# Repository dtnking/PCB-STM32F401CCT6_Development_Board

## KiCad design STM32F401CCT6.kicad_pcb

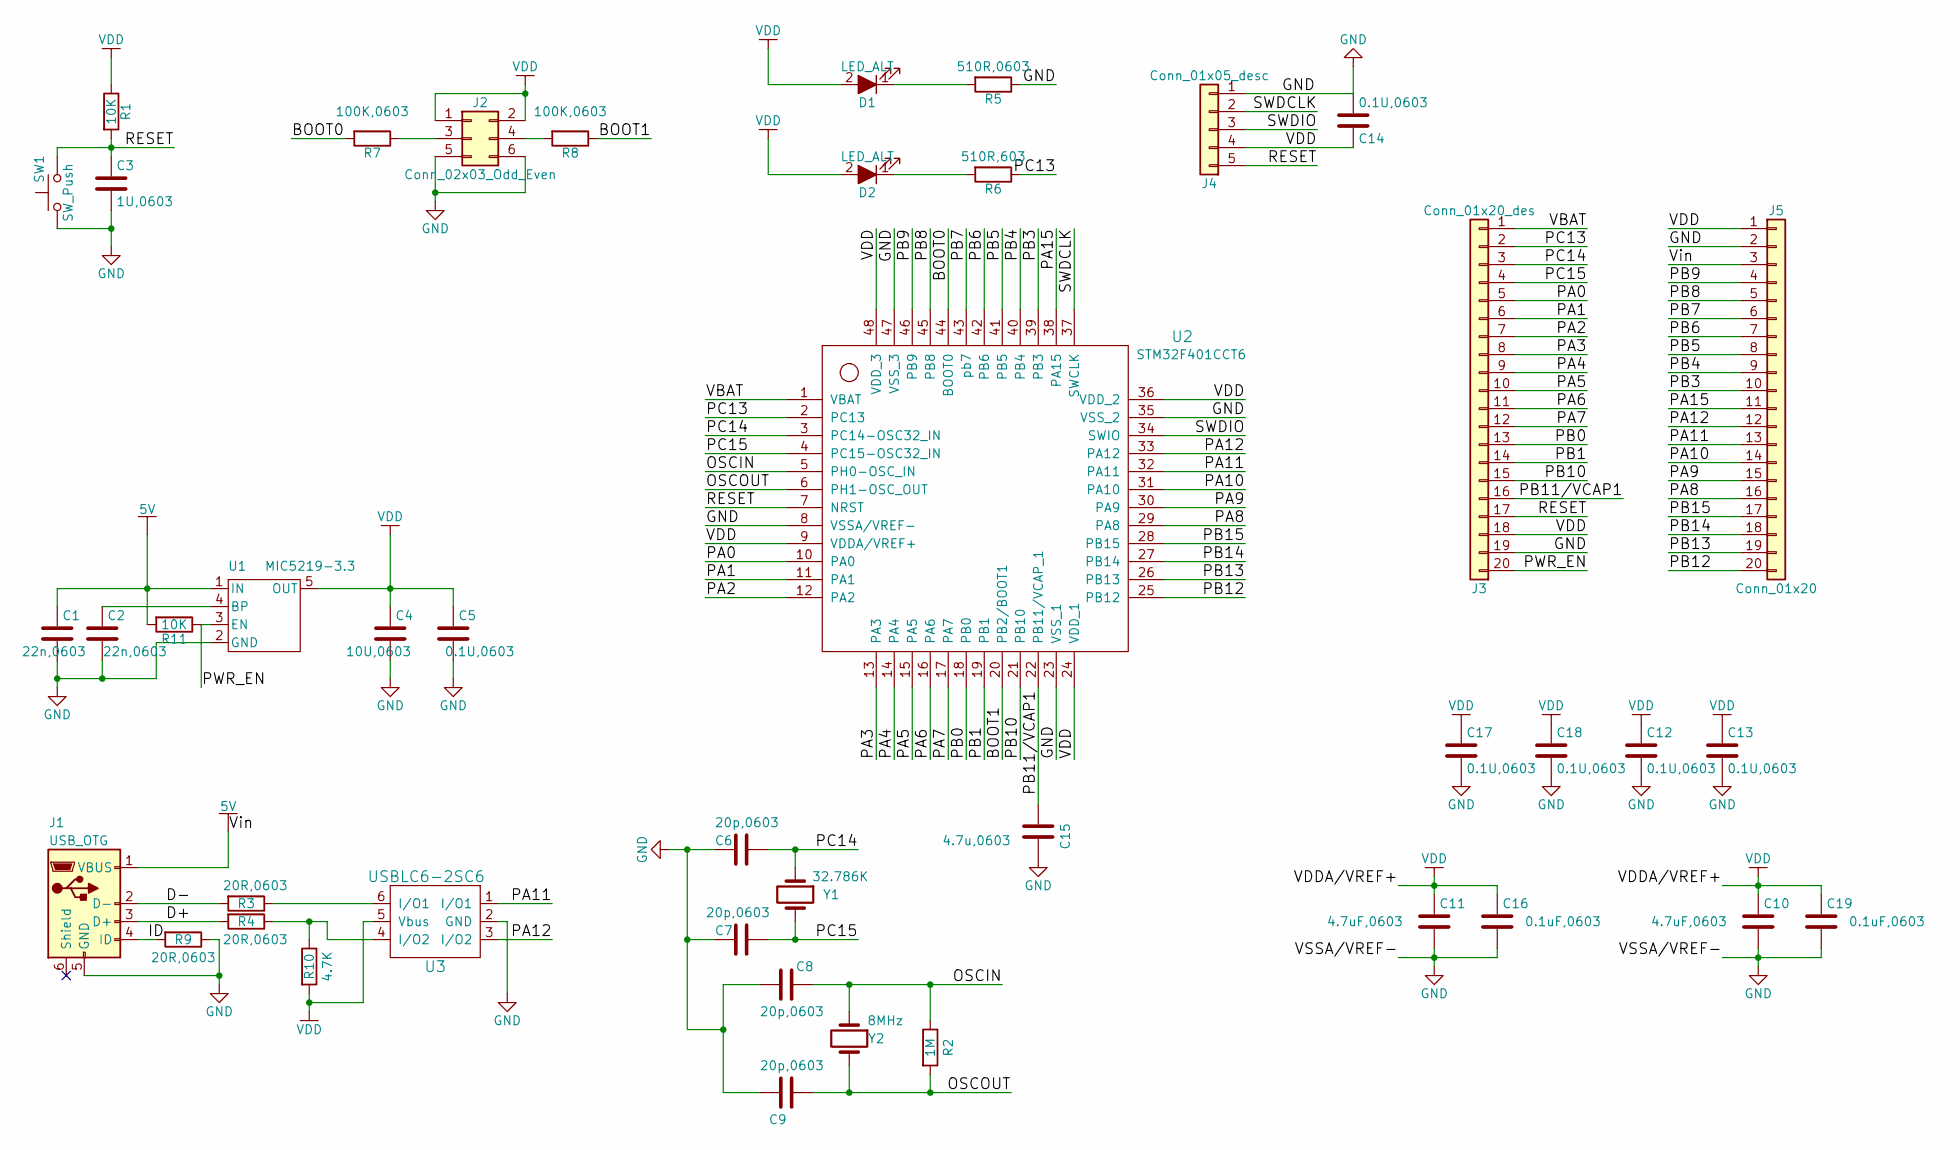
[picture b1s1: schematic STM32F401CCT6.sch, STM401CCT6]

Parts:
C1, C2: 22n,0603; C_0603
C3: 1U,0603; C_0603
C4: 10U,0603; C_0603
C5, C12, C13, C14, C17, C18: 0.1U,0603; C_0603
C6, C7, C8, C9: 20p,0603; C_0603
C10, C11: 4.7uF,0603; C_0603
C15: 4.7u,0603; C_0603
C16, C19: 0.1uF,0603; C_0603
D1, D2: LED_ALT; LED_0805
J1: USB_OTG; USB_Micro-B_Molex-105017-0001
J2: Conn_02x03_Odd_Even; Pin_Header_Straight_2x03_Pitch2.54mm
J3: Conn_01x20_des; Pin_Header_Straight_1x20_Pitch2.54mm
J4: Conn_01x05_desc; Pin_Header_Angled_1x05_Pitch2.54mm
J5: Conn_01x20; Pin_Header_Straight_1x20_Pitch2.54mm
R1, R11: 10K; R_0603
R2: 1M; R_0603
R3, R4, R9: 20R,0603; R_0603
R5: 510R,0603; R_0603
R6: 510R,603; R_0603
R7, R8: 100K,0603; R_0603
R10: 4.7K; R_0603
SW1: SW_Push; SW_SPST_TL3342
U1: MIC5219-3.3; SOT-23-5
U2: STM32F401CCT6; QFN_QFP48
U3: USBLC6-2SC6; SOT-23-6
Y1: 32.786K; Crystal_SMD_SeikoEpson_MC306-4pin_8.0x3.2mm
Y2: 8MHz; Crystal_HC49-4H_Vertical

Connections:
+5V: C1.1, J1.1 (VBUS), J5.3, R11.2, U1.1 (IN)
/BOOT0: R7.2, U2.44 (BOOT0)
/BOOT1: R8.1, U2.20 (PB2/BOOT1)
/D+: J1.3 (D+), R4.2
/D-: J1.2 (D-), R3.2
/ID: J1.4 (ID), R9.2
/OSCIN: C8.1, R2.1, U2.5 (PH0-OSC_IN), Y2.1
/OSCOUT: C9.1, R2.2, U2.6 (PH1-OSC_OUT), Y2.2
/PA0: J3.5, U2.10 (PA0)
/PA1: J3.6, U2.11 (PA1)
/PA2: J3.7, U2.12 (PA2)
/PA3: J3.8, U2.13 (PA3)
/PA4: J3.9, U2.14 (PA4)
/PA5: J3.10, U2.15 (PA5)
/PA6: J3.11, U2.16 (PA6)
/PA7: J3.12, U2.17 (PA7)
/PA8: J5.16, U2.29 (PA8)
/PA9: J5.15, U2.30 (PA9)
/PA10: J5.14, U2.31 (PA10)
/PA11: J5.13, U2.32 (PA11), U3.1 (I/O1)
/PA12: J5.12, U2.33 (PA12), U3.3 (I/O2)
/PA15: J5.11, U2.38 (PA15)
/PB0: J3.13, U2.18 (PB0)
/PB1: J3.14, U2.19 (PB1)
/PB3: J5.10, U2.39 (PB3)
/PB4: J5.9, U2.40 (PB4)
/PB5: J5.8, U2.41 (PB5)
/PB6: J5.7, U2.42 (PB6)
/PB7: J5.6, U2.43 (pb7)
/PB8: J5.5, U2.45 (PB8)
/PB9: J5.4, U2.46 (PB9)
/PB10: J3.15, U2.21 (PB10)
/PB11/VCAP1: C15.2, J3.16, U2.22 (PB11/VCAP_1)
/PB12: J5.20, U2.25 (PB12)
/PB13: J5.19, U2.26 (PB13)
/PB14: J5.18, U2.27 (PB14)
/PB15: J5.17, U2.28 (PB15)
/PC13: J3.2, R6.1, U2.2 (PC13)
/PC14: C6.1, J3.3, U2.3 (PC14-OSC32_IN), Y1.1
/PC15: C7.1, J3.4, U2.4 (PC15-OSC32_IN), Y1.2, Y1.4
/PWR_EN: J3.20, R11.1, U1.3 (EN)
/RESET: C3.1, J3.17, J4.5, R1.2, SW1.2, U2.7 (NRST)
/SWDCLK: J4.2, U2.37 (SWCLK)
/SWDIO: J4.3, U2.34 (SWIO)
/VBAT: J3.1, U2.1 (VBAT)
/VDD: C4.1, C5.1, C10.1, C11.1, C12.1, C13.1, C14.1, C16.1, C17.1, C18.1, C19.1, D1.2 (A), D2.2 (A), J2.1, J2.2, J3.18, J4.4, J5.1, R1.1, R10.2, U1.5 (OUT), U2.9 (VDDA/VREF+), U2.24 (VDD_1), U2.36 (VDD_2), U2.48 (VDD_3), U3.5 (Vbus)
GND: C1.2, C2.2, C3.2, C4.2, C5.2, C6.2, C7.2, C8.2, C9.2, C10.2, C11.2, C12.2, C13.2, C14.2, C15.1, C16.2, C17.2, C18.2, C19.2, J1.5 (GND), J1.6 (Shield), J2.5, J2.6, J3.19, J4.1, J5.2, R5.1, R9.1, SW1.1, U1.2 (GND), U2.0, U2.8 (VSSA/VREF-), U2.23 (VSS_1), U2.35 (VSS_2), U2.47 (VSS_3), U3.2 (GND)
unnamed: C2.1, U1.4 (BP)
unnamed: D1.1 (K), R5.2
unnamed: D2.1 (K), R6.2
unnamed: J2.3, R7.1
unnamed: J2.4, R8.2
unnamed: R3.1, U3.6 (I/O1)
unnamed: R4.1, R10.1, U3.4 (I/O2)

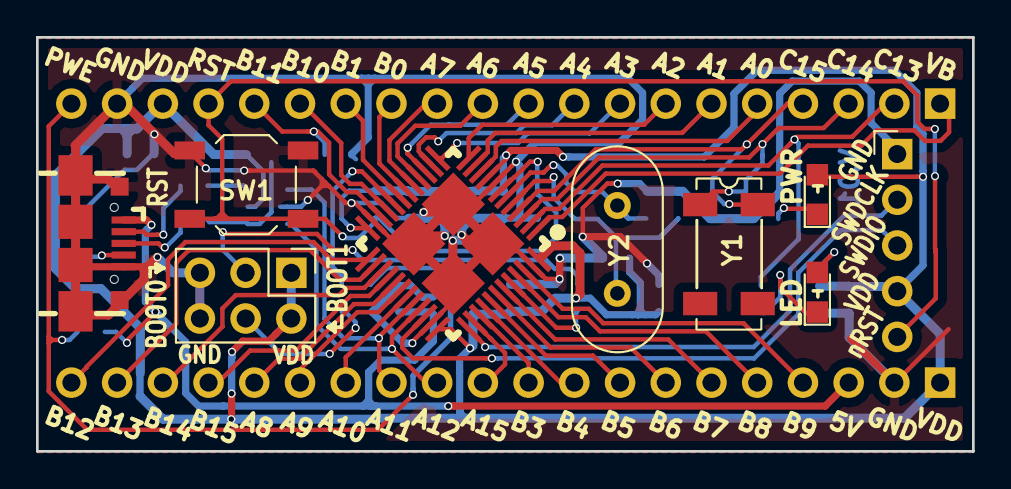
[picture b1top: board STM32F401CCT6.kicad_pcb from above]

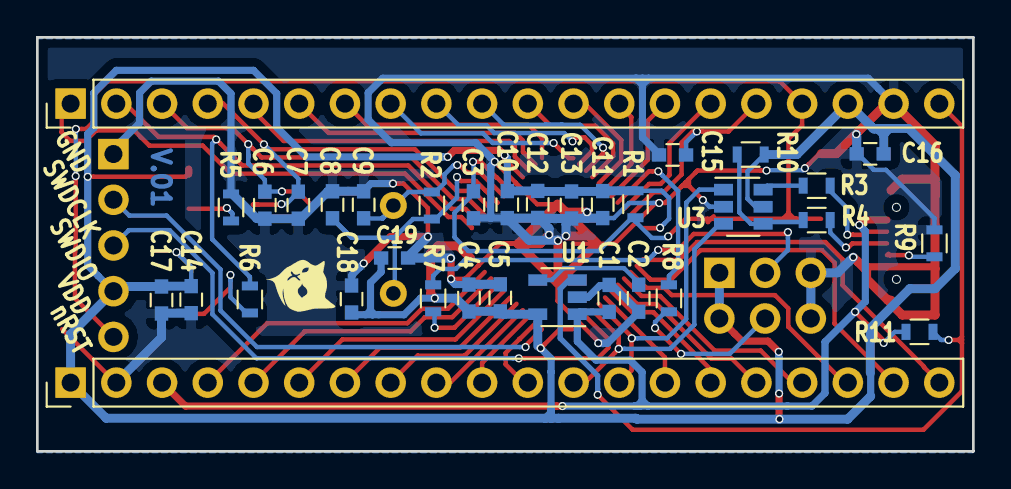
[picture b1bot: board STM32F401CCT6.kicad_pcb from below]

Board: 2 copper layers, 52.0 x 23.0 mm, 47 parts (35 on the bottom side), 54 nets.

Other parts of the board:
Dot: G***; Dot
HS_Crystal: G***; HS_Crystal
LS_Crystal: G***; LS_Crystal
Meow: G***; Meow

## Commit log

2017-10-03 Drawed the schematic of STM32F401CCT6-without TVS
2017-10-03 Added USBLC6 component lib
2017-10-05 Changed pin SWDIO and SWDCLK
2017-10-06 Assosciated schematic to footprint
2017-10-06 Changed LED(schematic)
2017-10-06 Added QFP-QFN48 footprint
2017-10-07 Fixed QFN-QPN mod
2017-10-07 Added a dot near pin1 as an indication
2017-10-09 routing
2017-10-10 Added copper pour
2017-10-10 Modified QFN-QFP48
2017-10-10 Rerouted
2017-10-11 rerouting (left reset)
2017-10-11 Fixed QFPN48 pin 47 and 48 distances to 0.2
2017-10-11 Finish routing
2017-10-12 Added pin name on silk layer
2017-10-12 Finish design the layout-Added Image on it
2017-10-13 Changed footprint from handsoldering to none
2017-10-13 Moved the pin connector to bottom layer
2017-10-13 Rotated the neko image
2017-10-17 Changed via size to 0.45/0.3mm and generated Gerber file
2017-10-20 Modified routing
2017-10-22 Moved the pin indicator(silk layer) further away from the edge cut
2017-10-23 Moved Micro_USB further out and reroute some tracks
2017-10-24 Moved the bottom edge cut further inwards
2017-10-30 Widen the track of power source
2017-10-30 Added corner outline as an indicator for the footprint QFP48
2017-10-31 Adjusted the size of the label indicator
2017-11-05 Updated the via diamter and drill size 0.435/0.3 mm
2017-11-06 Added extra capacitor between VDD and GND (VFFA-VSSA)
2017-11-06 Fixed the pad near tracks error (reallocated the QFN)
2017-11-07 Change pin20 to Pwr Enable and added a resistor on it
2017-11-07 Changed pin 20 to PWE schemaic
2017-11-09 Re-routed (prioritised D+ D- SWDIO SWCLK) by reducing the track length and via along the tracks.
2017-11-09 Changed the via size to 0.453/0.3 mm
2017-11-12 Renamed VCC to VDD
2017-11-13 Added indication for LED footprint and added dimension on Eco1.user layer
2017-11-14 Change the route nicely
2017-11-15 Panelized with other PCB
2017-11-16 Removed the silk layer of angled pin header and move the bottom pin label downward
2017-11-16 Produced merged gerber file of STM32 board together with RJ12 and ST-Link
2017-11-16 Changed the 4 corner labels indication for footprint of QFN-QFP
2017-11-17 Found missing bottom silk layer, placed it back
2017-11-17 Enlarged the QFN-QFP48 footprint pin 1 indication label and the dimension label from 0.3mm to 0.4mm
2017-11-17 Regenerated combined gerber file (with ST-Link and RJ12)
2017-11-17 Removed older PCB file
2017-11-17 Renamed the merge gerber folder
2017-11-17 Renamed the pin3 track label from ST-Link to Vin
2017-11-18 Moved silk layer away from via and swap the position of VDD with nRST pin of the SWDIO
2017-11-20 Added a new footprint for Micro USB (non-Complete)
2017-11-21 Extend the pads of the Micro-USB and draw the silk layer for indicatiom
2017-11-22 Replace the Micro-USB footprint with the one newly created, added a shield for MCU (grounded pin), moved some component inwards to prevent touching the pinheader plastic.
2017-11-22 Re-generated gerber files for panelizing
2017-11-27 Generated new gerber file
2017-11-29 Moved the indicator of LED slightly to the right
2017-12-01 Replaced the MCU footprint
2017-12-03 Changed the kitty silk layer
2017-12-05 changed the copper pour clearance
2017-12-10 Change back the Micro_usb footprint to THT footprint
2018-01-16 Generated gerber file with drill hole of trailing zero format
2018-02-09 Resolved the problem of silk layer does not shown up
